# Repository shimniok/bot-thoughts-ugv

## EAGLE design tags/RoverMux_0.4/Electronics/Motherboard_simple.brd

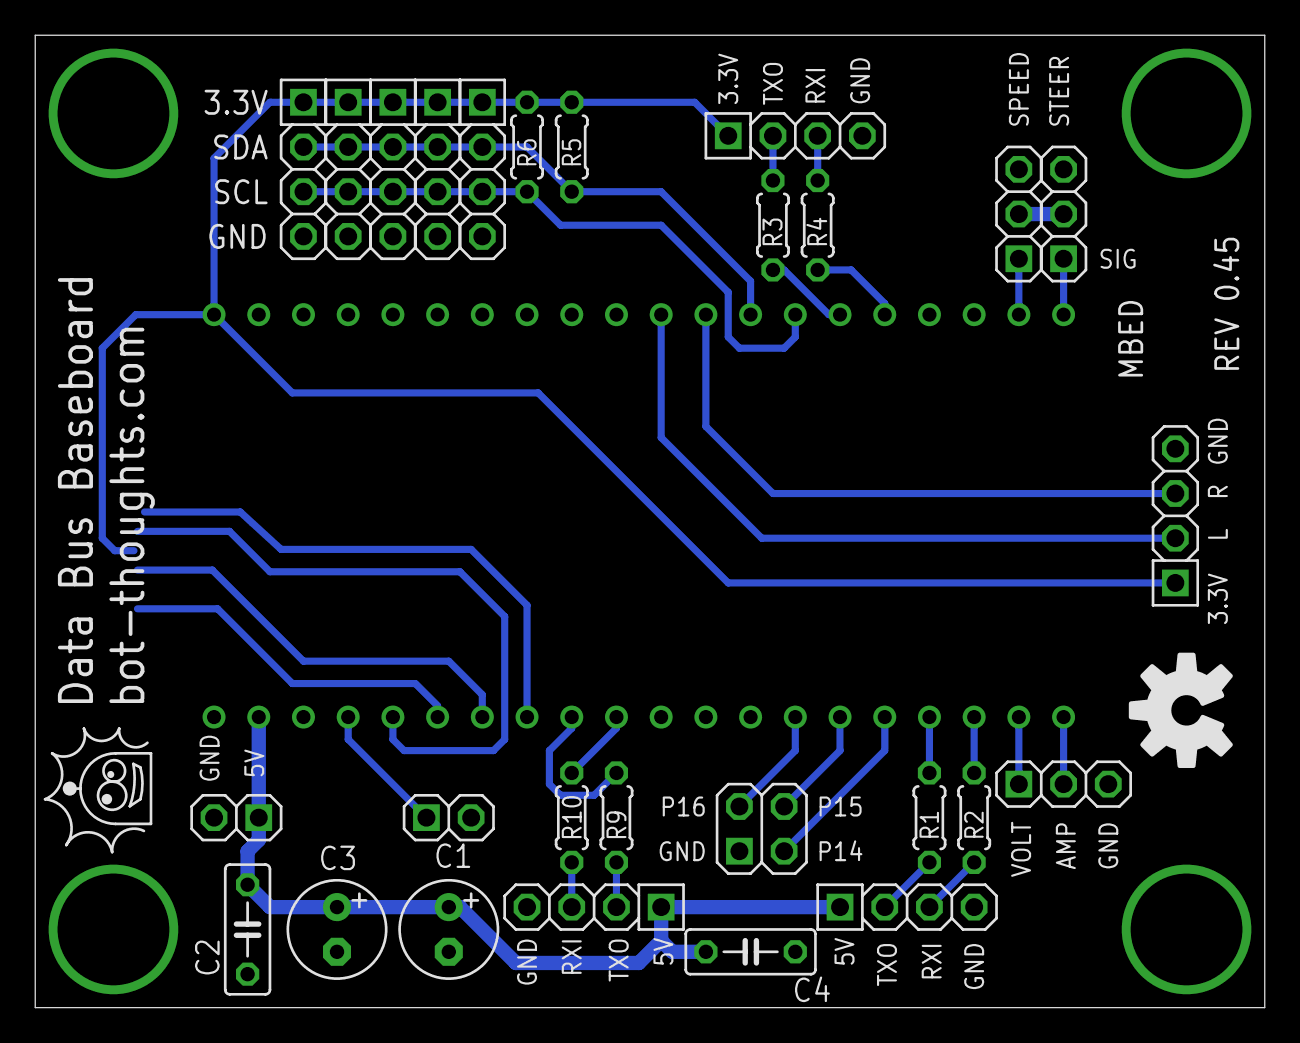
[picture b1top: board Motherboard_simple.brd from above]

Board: 2 copper layers, 69.8 x 55.2 mm, 29 parts (1 on the bottom side), 32 nets.

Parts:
C1: 470uF; E2,5-6
C2, C4: 0.01uF; C050-025X075
C3: 10uF; E2,5-6
JP1: BUTTONS; 2X02
JP2: UART1; 1X04-S
JP3: POWER; 1X02-S
JP4: RST; 1X02-S
JP5, JP11, JP12, JP13, JP14: I2C; 1X04-S
JP6: UART3; 1X04-S
JP8: SPEED; 1X03-S
JP9: STEER; 1X03-S
JP10: UART2; 1X04-S
JP15: ENCODERS; 1X04-S
JP17: VA; 1X03-S
MBED: MBED_NXP_LPC1768; MBED-KIT
R1, R2, R3, R4, R9, R10: 220; 0204/5
R5, R6: 2.2K; 0204/5
U2: USD-SOCKETNEW; MICRO-SD-SOCKET-PP

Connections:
!CS1: MBED.P$8, U2.2
!RESET: JP4.1, MBED.NR
+3V3: JP2.1, JP5.1, JP11.1, JP12.1, JP13.1, JP14.1, JP15.1, MBED.VOUT, R5.2, R6.2, U2.4
+5V: C1.+, C2.1, C3.+, C4.1, JP3.1, JP6.1, JP10.1, MBED.VIN
AMP: JP17.2, MBED.P$20
ENC_LEFT: JP15.2, MBED.P$30
ENC_RIGHT: JP15.3, MBED.P$29
GND: C1.-, C2.2, C3.-, C4.2, JP1.1, JP2.4, JP3.2, JP4.2, JP5.4, JP6.4, JP8.3, JP9.3, JP10.4, JP11.4, JP12.4, JP13.4, JP14.4, JP15.4, JP17.3, MBED.GND, U2.6, U2.GND1, U2.GND3
MISO1: MBED.P$6, U2.7
MOSI1: MBED.P$5, U2.3
unnamed: JP6.2, R1.2
unnamed: JP6.3, R2.2
unnamed: JP8.2, JP9.2
unnamed: JP1.2, MBED.P$14
unnamed: JP17.1, MBED.P$19
unnamed: JP1.4, MBED.P$15
unnamed: JP1.3, MBED.P$16
unnamed: JP2.2, R3.2
unnamed: JP2.3, R4.2
unnamed: JP10.2, R9.2
unnamed: JP10.3, R10.2
RXD1: MBED.P$25, R4.1
RXD2: MBED.P$10, R10.1
RXD3: MBED.P$18, R2.1
SCK1: MBED.P$7, U2.5
SCL: JP5.3, JP11.3, JP12.3, JP13.3, JP14.3, MBED.P$27, R6.1
SDA: JP5.2, JP11.2, JP12.2, JP13.2, JP14.2, MBED.P$28, R5.1
SPEED: JP8.1, MBED.P$22
STEER: JP9.1, MBED.P$21
TXD1: MBED.P$26, R3.1
TXD2: MBED.P$9, R9.1
TXD3: MBED.P$17, R1.1

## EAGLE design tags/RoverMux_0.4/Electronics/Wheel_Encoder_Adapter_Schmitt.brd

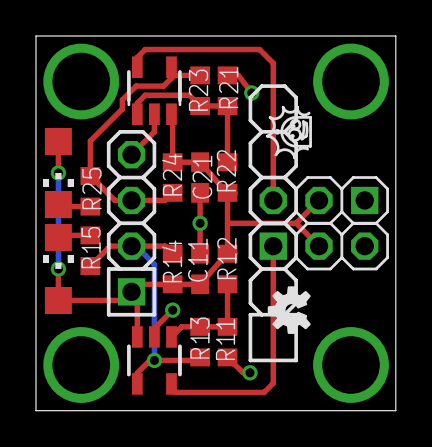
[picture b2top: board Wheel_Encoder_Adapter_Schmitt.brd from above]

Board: 2 copper layers, 20.0 x 20.8 mm, 19 parts (0 on the bottom side), 10 nets.

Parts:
C11, C21: 1uF; C0603
IC1, IC2: TL331; DBV-R-PDSO-G5
JP1: RIGHT; 1X03-S
JP2: LEFT; 1X03-S
JP3: TO MCU; 1X04-S
LED1: LEFT; CHIPLED_1206
LED2: RIGHT; CHIPLED_1206
R11, R21: 12K; R0603
R12, R22: 56K; R0603
R13, R23: 51K; R0603
R14, R24: 10K; R0603
R15, R25: 330; R0603

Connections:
GND: C11.2, C21.2, IC1.2, IC2.2, JP1.1, JP2.3, JP3.4, R11.1, R21.1
IN_LEFT: IC1.5, JP2.1
IN_RIGHT: IC2.5, JP1.3
unnamed: LED1.C, R15.1
unnamed: IC1.1, R11.2, R12.1, R13.1
unnamed: LED2.C, R25.1
unnamed: IC2.1, R21.2, R22.1, R23.1
OUT_LEFT: IC1.4, JP3.2, R13.2, R14.1, R15.2
OUT_RIGHT: IC2.4, JP3.3, R23.2, R24.1, R25.2
VCC: C11.1, C21.1, IC1.3, IC2.3, JP1.2, JP2.2, JP3.1, LED1.A, LED2.A, R12.2, R14.2, R22.2, R24.2

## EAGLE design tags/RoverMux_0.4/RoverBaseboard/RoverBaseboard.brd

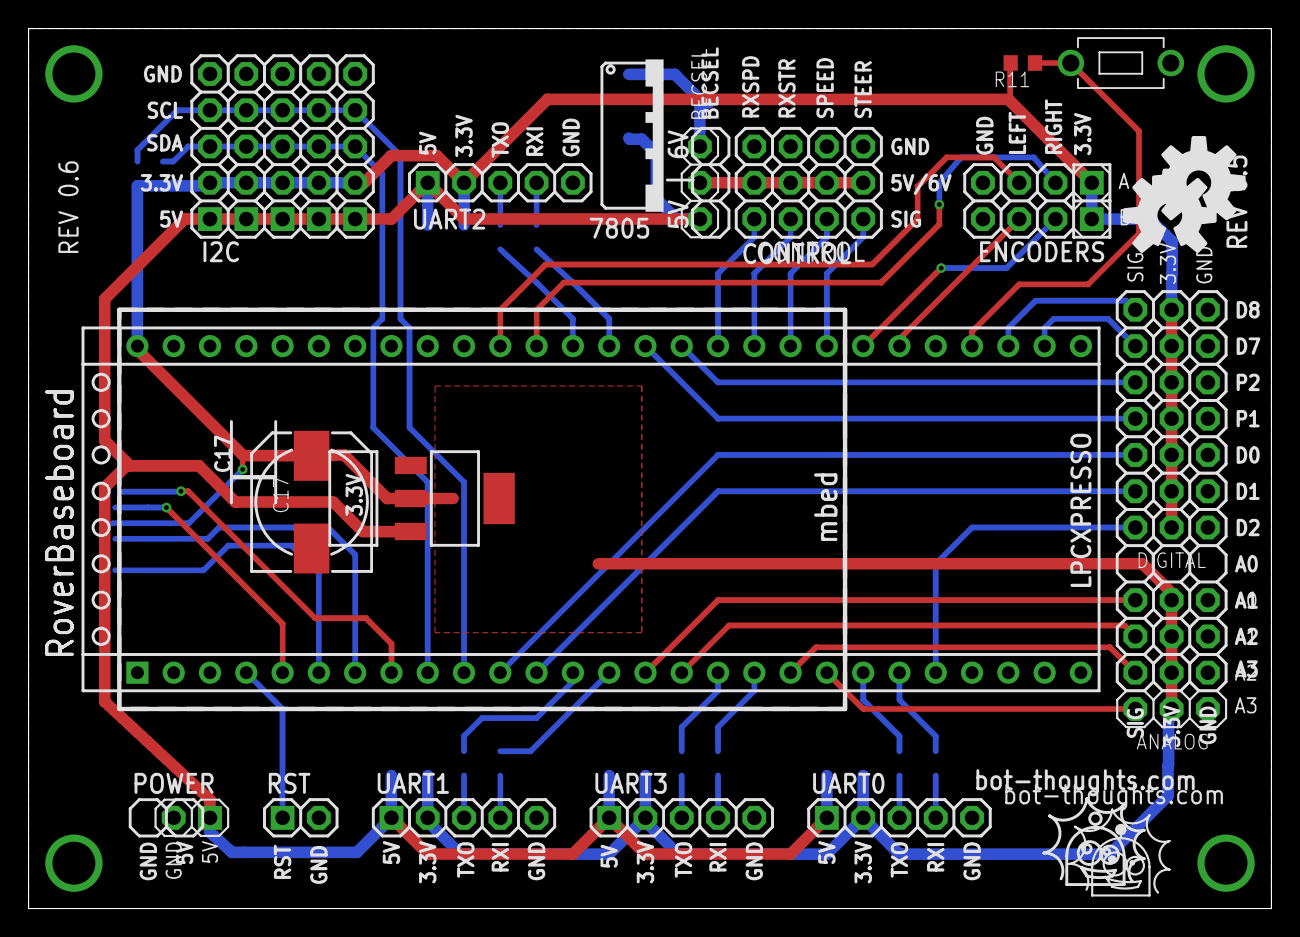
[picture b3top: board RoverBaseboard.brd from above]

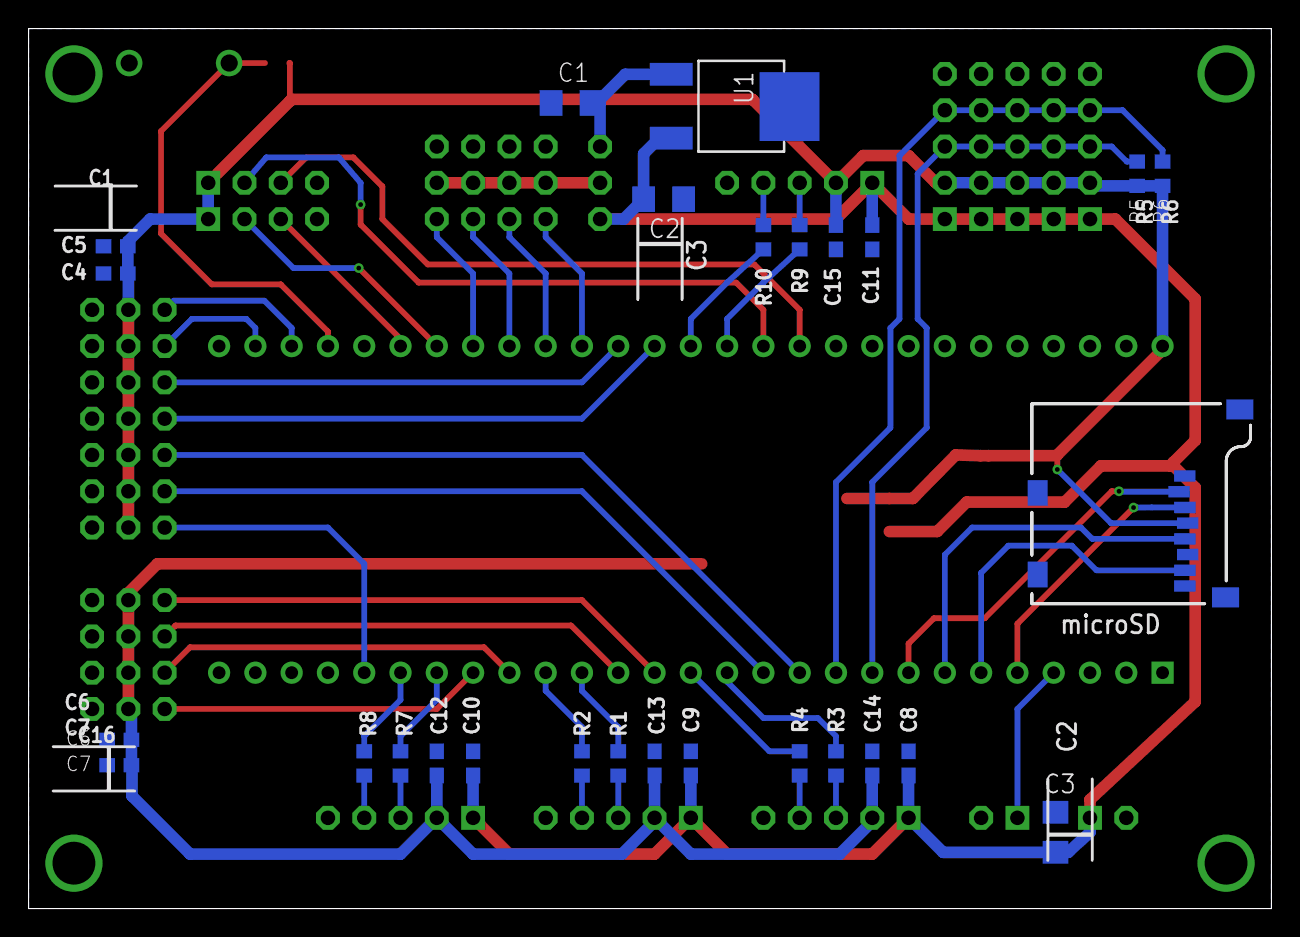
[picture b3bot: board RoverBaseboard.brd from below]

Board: 2 copper layers, 87.0 x 61.6 mm, 61 parts (27 on the bottom side), 48 nets.

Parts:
BECSEL: 5V | 6V; 1X03-S
C1, C2, C3: 106; C1206
C4, C6, C8, C9, C10, C11, C12, C13, C14, C15: 106; C0603
C5, C7: 104; C0603
C17: 33uF; 140CLH-0810
IC3: 3.3V; SOT223
JP1, JP13: IO; 1X03-S
JP2, JP15: ENCODERS; 1X04-S
JP3: POWER; 1X02-S
JP4: RST; 1X02-S
JP5: RXSPD; 1X03-S
JP6: RXSTR; 1X03-S
JP7: UART0; 1X05-S
JP8: SPEED; 1X03-S
JP9: STEER; 1X03-S
JP10, JP11: PWM; 1X03-S
JP14, JP28, JP29: DIGITAL; 1X03-S
JP16, JP17, JP18, JP19: ADC; 1X03-S
JP20: UART1; 1X05-S
JP21: UART2; 1X05-S
JP22: UART3; 1X05-S
JP23: I2C; 1X05-S
JP24, JP25, JP26, JP27: 1X05-S
R1, R2, R3, R4, R7, R8, R9, R10, R11: 10K; R0603
R5, R6: 2.2K; R0603
S1: ISP; 6MMTACTILE_RECT
U1: LD29150DT50R; DPAK
U2: microSD; MICRO-SD-SOCKET-PP
U$1: LPCXPRESSO; LPCXPRESSO_NO_PAD

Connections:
!CS1: U2.2, U$1.J6-8
!ISP: R11.1, S1.P$2, U$1.J6-51
!RESET: JP4.1, U$1.J6-4
+3V3: C4.1, C5.1, C6.1, C7.1, C12.1, C13.1, C14.1, C15.1, C17.+, IC3.2, IC3.4, JP1.2, JP2.1, JP7.2, JP10.2, JP11.2, JP13.2, JP14.2, JP15.1, JP16.2, JP17.2, JP18.2, JP19.2, JP20.2, JP21.2, JP22.2, JP23.2, JP24.2, JP25.2, JP26.2, JP27.2, JP28.2, JP29.2, R5.2, R6.2, R11.2, U2.4, U$1.J6-28
+5V: BECSEL.3, C2.1, C3.1, C8.1, C9.1, C10.1, C11.1, IC3.3, JP3.1, JP7.1, JP20.1, JP21.1, JP22.1, JP23.1, JP24.1, JP25.1, JP26.1, JP27.1, U1.3
A0: JP16.1, U$1.J6-15
A1: JP17.1, U$1.J6-16
A2: JP18.1, U$1.J6-19
A3: JP19.1, U$1.J6-20
BEC: BECSEL.2, JP5.2, JP6.2, JP8.2, JP9.2
D0: JP1.1, U$1.J6-11
D1: JP13.1, U$1.J6-12
D2: JP14.1, U$1.J6-23
D7: JP28.1, U$1.J6-53
D8: JP29.1, U$1.J6-52
ENC0: JP15.3, U$1.J6-38
ENC1: JP15.2, U$1.J6-39
ENC2: JP2.2, U$1.J6-48
ENC3: JP2.3, U$1.J6-49
GND: C1.2, C2.2, C3.2, C4.2, C5.2, C6.2, C7.2, C8.2, C9.2, C10.2, C11.2, C12.2, C13.2, C14.2, C15.2, C17.-, IC3.1, JP1.3, JP2.4, JP3.2, JP4.2, JP5.3, JP6.3, JP7.5, JP8.3, JP9.3, JP10.3, JP11.3, JP13.3, JP14.3, JP15.4, JP16.3, JP17.3, JP18.3, JP19.3, JP20.5, JP21.5, JP22.5, JP23.5, JP24.5, JP25.5, JP26.5, JP27.5, JP28.3, JP29.3, S1.P$1, U1.4, U2.6, U2.GND1, U2.GND3, U$1.J6-1, U$1.J6-54
MISO1: U2.7, U$1.J6-6
MOSI1: U2.3, U$1.J6-5
unnamed: JP22.3, R1.2
unnamed: JP22.4, R2.2
unnamed: JP7.3, R7.2
unnamed: JP7.4, R8.2
unnamed: JP20.3, R3.2
unnamed: JP20.4, R4.2
unnamed: JP21.3, R9.2
unnamed: JP21.4, R10.2
PWM1: JP10.1, U$1.J6-42
PWM2: JP11.1, U$1.J6-43
RXD0: R8.1, U$1.J6-22
RXD1: R4.1, U$1.J6-14
RXD2: R10.1, U$1.J6-41
RXD3: R2.1, U$1.J6-18
RXSPD: JP5.1, U$1.J6-44
RXSTR: JP6.1, U$1.J6-45
SCK1: U2.5, U$1.J6-7
SCL: JP23.4, JP24.4, JP25.4, JP26.4, JP27.4, R6.1, U$1.J6-10
SDA: JP23.3, JP24.3, JP25.3, JP26.3, JP27.3, R5.1, U$1.J6-9
SPEED: JP8.1, U$1.J6-46
STEER: JP9.1, U$1.J6-47
TXD0: R7.1, U$1.J6-21
TXD1: R3.1, U$1.J6-13
TXD2: R9.1, U$1.J6-40
TXD3: R1.1, U$1.J6-17
VBEC: BECSEL.1, C1.1, U1.1
